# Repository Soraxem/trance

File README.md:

[This on Youtube](https://www.youtube.com/playlist?list=PL4cNBOFjqRCpjGmj9xtUntssc8VHCmmZN) | [This on Makertube](https://makertube.net/w/p/su6X6o1RSBtH18CKgF7tRq) | [This on PCBWAY](https://www.pcbway.com/project/member/shareproject/?bmbno=57956445-373F-42)

# Trance

The Trance Device Family are open hardware devices that allow life wireless lighting control via ArtNet 4. These devices mainly have applications in portable, mobile, and flexible lighting solutions.

## Control

Some lighting controllers do not implement ArtNet 4 with udp unicasting. UDP unicasting is essential for wireless lighting, because most WiFi routers ratelimit and occasionally hold back multicasted UDP packets. Unicasted UDP packets do not get ratelimited and are therefore the way to go.

If your controller does not implement UDP multicasting as per ArtNet 4 Specification, you can use my translation layer called artman. [Github Repo here](https://github.com/Soraxem/artman).

## Software

To ensure a flexible and easy software, there is a Arduino library, that implements the communication side of the software. By updating this Library with more Protocols or more reliable networking, we can expand the functionallity of every trance controller, despite hardware differences. This Library also allows for easy hardware development for DIY solutions.

You can find the Library [here on github](https://github.com/Soraxem/trance-library).

## Hardware

This project also features custom hardware that is more compact than just using a ESP32 devboard.

### USB-DMX

This device interfaces with the Eurolite Wireless DMX port on some of the newer Eurolite devices.

### PIXEL-LED

This is a led controller that can interface with the common spi-leds like ws8212. It can directly be plugged in to the usb port of a wall adapter.

## License

This Project is licensed under CERN-OHL-P

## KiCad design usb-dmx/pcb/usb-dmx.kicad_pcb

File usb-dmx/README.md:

# TRANCE USB-DMX

[Quickstart Maunual](quickstart-manual.pdf)

## Overview

The USB DMX Model is a device that has an USB plug that delivers dmx data instead of usb data. This makes the Device compatible with all DMX-over-USB devices in lighting technology.

The Company Steinigke showtechnic has some fixtures with such a Port. These Ports are originally designed for their WirelessDMX and QuickDMX devices, wich essentially are CRMX adapters. This Project is in now way affiliated with XRMC or Steinigke showtechnic.

## Usage

In The Configurations page the Artnet DMX-Address has to be set to 1, for the device to work correctly.

## Assembly

There only are smd components for this device. Here is what you need to assemble this device.

- PCBS
- Stencil
- All components from the BOM
- Tweezers
- Solder Paste
- a Plastic card
- Tissues
- SMD reflow oven or Hot Plate
- Soldering Iron
- Solder
- Masking Tape
- a Steady hand

Study the schematic and the components closely, just to be sure where and how to place each component. Then apply the Solder Paste with the Stencil, place the components and reflow the device.

## Firmware

The firmware is dependant on multible Librarys, wich are mentioned at the beginning of the file. Make sure to install the correct versions of these librarys. It also depends on the Trance library, wich is not Published in the Library Manager. To install this library, download the right version from github and put it into your arduino library Folder.

For flashing press the button on the device and plug the USB-C into the computer while keeping the button pressed. By this the microcontroller connects to the computer and expexts a software to be flashed. In arduino select the correct port and configuration, then upload the firmware.

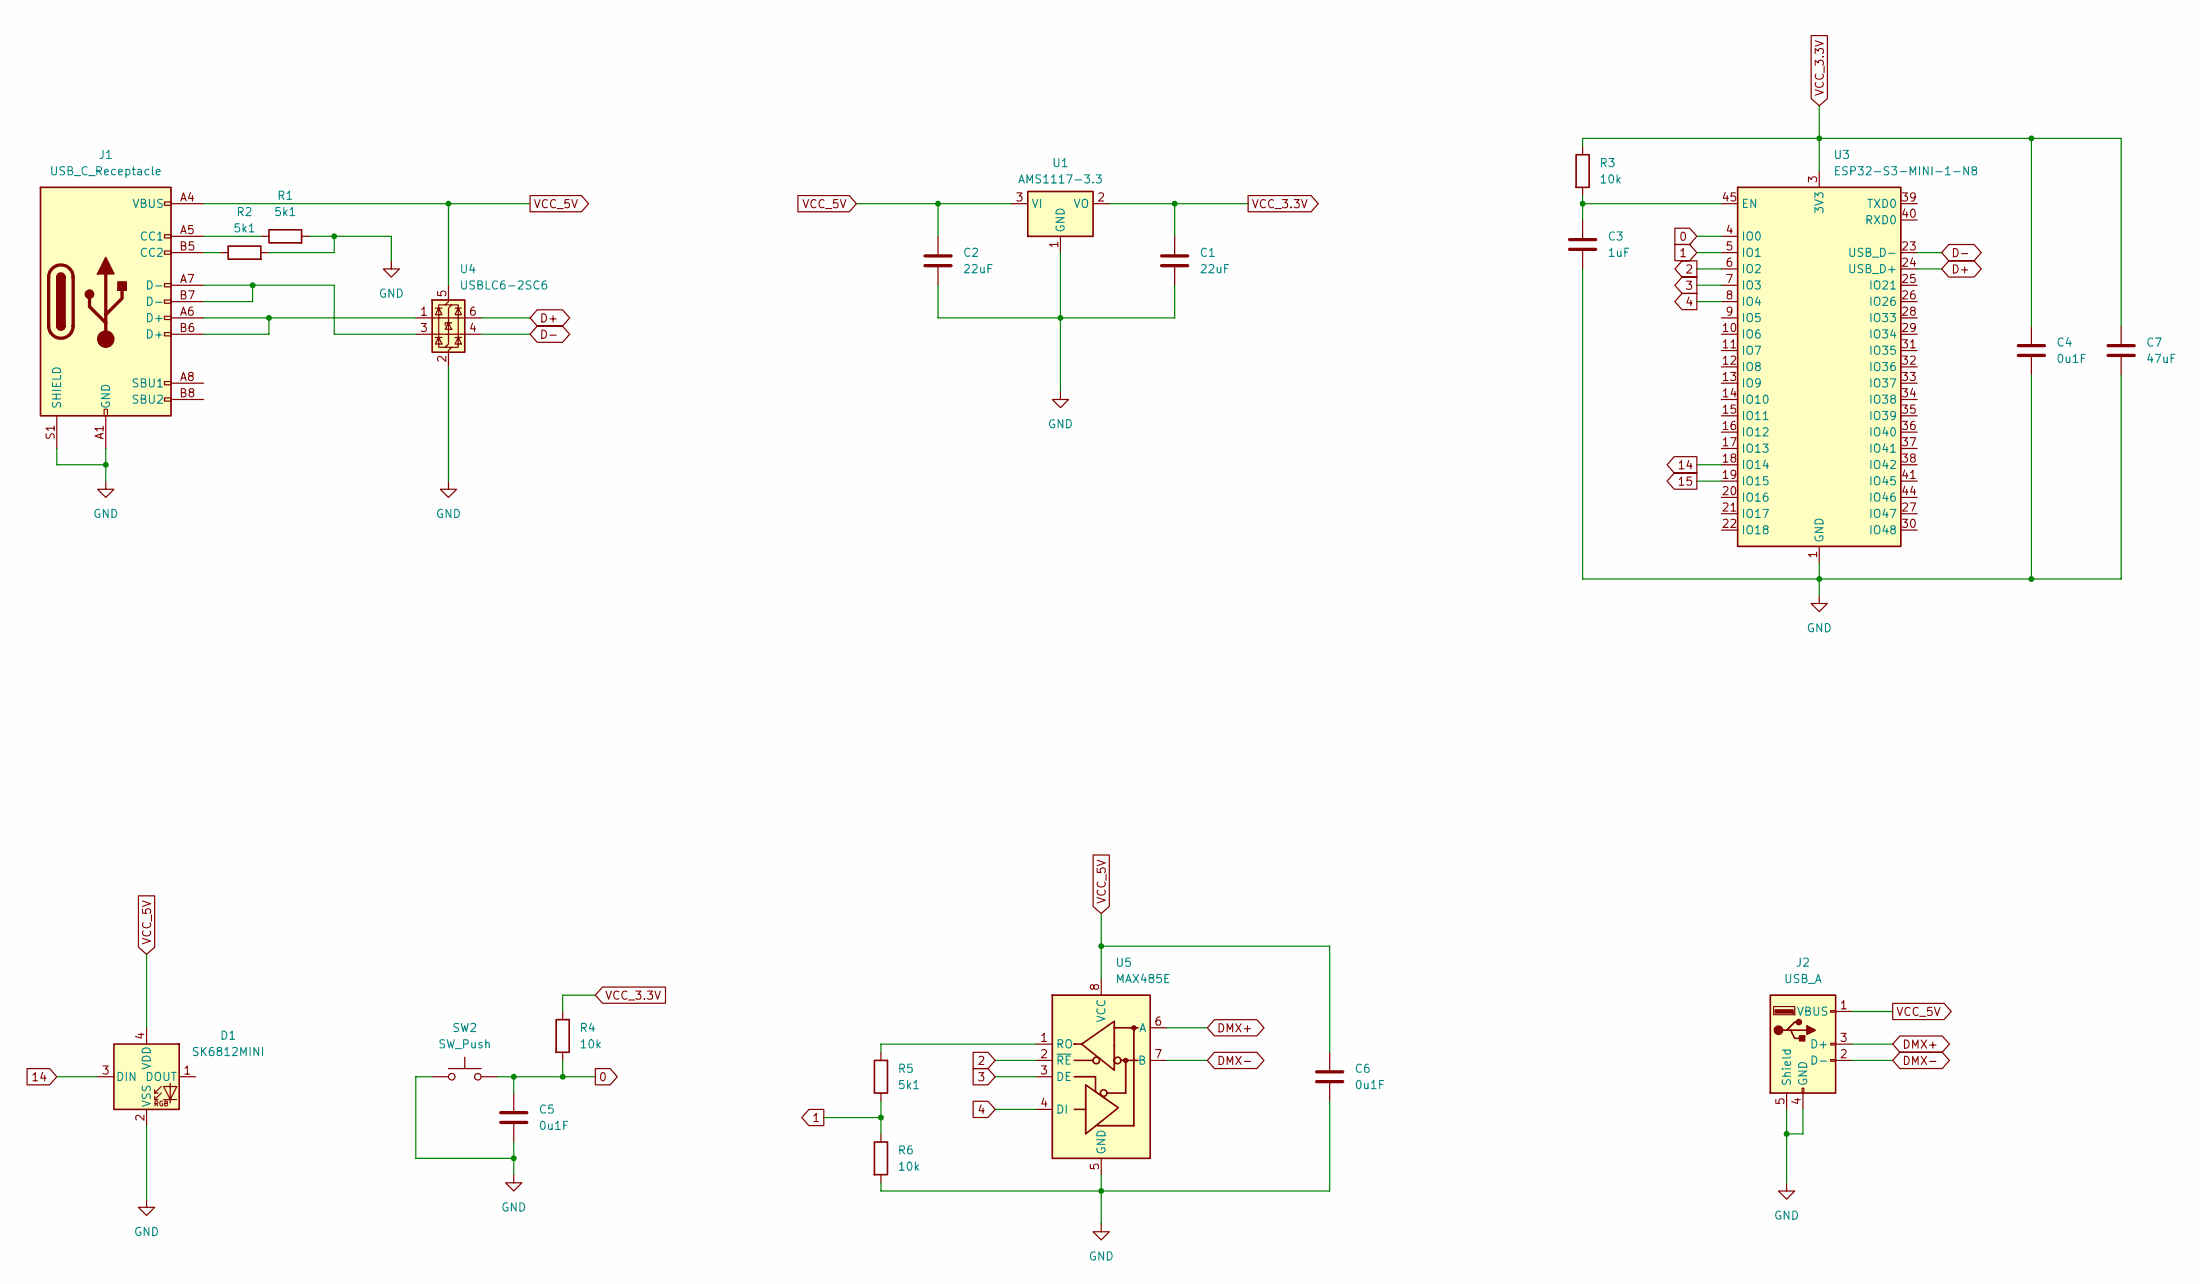
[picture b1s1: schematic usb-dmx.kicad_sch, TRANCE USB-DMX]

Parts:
C1, C2: 22uF; C_0805_2012Metric
C3: 1uF; C_0603_1608Metric_Pad1.08x0.95mm_HandSolder
C4, C6: 0u1F; C_0603_1608Metric_Pad1.08x0.95mm_HandSolder
C5: 0u1F; C_0603_1608Metric
C7: 47uF; C_0805_2012Metric_Pad1.18x1.45mm_HandSolder
D1: SK6812MINI; LED_SK6812MINI_PLCC4_3.5x3.5mm_P1.75mm
J1: USB_C_Receptacle; USB_C_Receptacle_GCT_USB4105-xx-A_16P_TopMnt_Horizontal
J2: USB_A; USB_A_CNCTech_1001-011-01101_Horizontal
R1, R2, R5: 5k1; R_0603_1608Metric_Pad0.98x0.95mm_HandSolder
R3, R6: 10k; R_0603_1608Metric_Pad0.98x0.95mm_HandSolder
R4: 10k; R_0603_1608Metric
SW2: SW_Push; SW_Push_1P1T_XKB_TS-1187A
U1: AMS1117-3.3; SOT-223-3_TabPin2
U3: ESP32-S3-MINI-1-N8; ESP32-S2-MINI-1U
U4: USBLC6-2SC6; SOT-23-6
U5: MAX485E; SOP-8_3.76x4.96mm_P1.27mm

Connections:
0: C5.1, R4.2, SW2.2, U3.4 (IO0)
1: R5.1, R6.1, U3.5 (IO1)
2: U3.6 (IO2), U5.2 (~RE)
3: U3.7 (IO3), U5.3 (DE)
4: U3.8 (IO4), U5.4 (DI)
14: D1.3 (DIN), U3.18 (IO14)
15: U3.19 (IO15)
D+: U3.24 (USB_D+), U4.6 (I/O1)
D-: U3.23 (USB_D-), U4.4 (I/O2)
DMX+: J2.3 (D+), U5.6 (A)
DMX-: J2.2 (D-), U5.7 (B)
GND: C1.2, C2.2, C3.2, C4.2, C5.2, C6.2, C7.2, D1.2 (VSS), J1.A1 (GND), J1.A12 (GND), J1.B1 (GND), J1.B12 (GND), J1.S1 (SHIELD), J2.4 (GND), J2.5 (Shield), R1.2, R2.2, R6.2, SW2.1, U1.1 (GND), U3.1 (GND), U3.2 (GND), U3.42 (GND), U3.43 (GND), U3.46 (GND), U3.47 (GND), U3.48 (GND), U3.49 (GND), U3.50 (GND), U3.51 (GND), U3.52 (GND), U3.53 (GND), U3.54 (GND), U3.55 (GND), U3.56 (GND), U3.57 (GND), U3.58 (GND), U3.59 (GND), U3.60 (GND), U3.61 (GND), U3.62 (GND), U3.63 (GND), U3.64 (GND), U3.65 (GND), U4.2 (GND), U5.5 (GND)
unnamed: J1.A5 (CC1), R1.1
unnamed: J1.B5 (CC2), R2.1
unnamed: J1.A6 (D+), J1.B6 (D+), U4.1 (I/O1)
unnamed: J1.A7 (D-), J1.B7 (D-), U4.3 (I/O2)
unnamed: C3.1, R3.2, U3.45 (EN)
unnamed: R5.2, U5.1 (RO)
VCC_3.3V: C1.1, C4.1, C7.1, R3.1, R4.1, U1.2 (VO), U3.3 (3V3)
VCC_5V: C2.1, C6.1, D1.4 (VDD), J1.A4 (VBUS), J1.A9 (VBUS), J1.B4 (VBUS), J1.B9 (VBUS), J2.1 (VBUS), U1.3 (VI), U4.5 (VBUS), U5.8 (VCC)

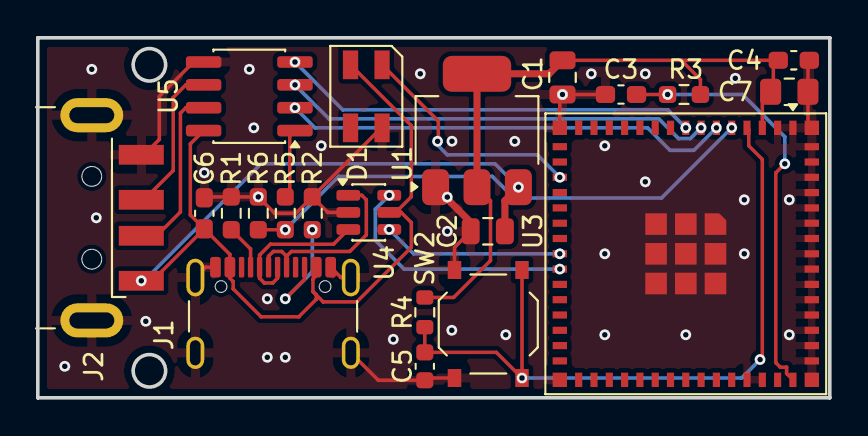
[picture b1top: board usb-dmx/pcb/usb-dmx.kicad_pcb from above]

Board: 2 copper layers, 44.0 x 20.0 mm, 21 parts (0 on the bottom side), 19 nets.

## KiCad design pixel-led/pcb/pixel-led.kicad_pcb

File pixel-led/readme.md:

# Trance PIXEL-LED

## Overview

Pixel LED is simply a Trance model that can control a spi led strip. It is designed to be directly plugged into a wall charger. It features an infrared sensor so it could be integrated with infrared remote controls.

## Sponsorship

[PCBWay](pcbway.com) was so kind to sponsor pcb production of revision 1.0 in development of this device. I quickly wanted to review their services here.

All the pcbs i recieved were up to specification and of good quality. I was suprized an honored to recieve such a sponsoring for such a small project. I admire how PCBWay invests in OpenSource electronics, especially with their project sharing platform.

## Remote

Currently there is only one Remote implemented in the Code. This remote is shipped with these [WS8212 Globe stringlights](aliexpress.com/item/1005009844838768.html), and normally interfaces with that controller.

There are firmware versions with and without the infrared Remote.

## Firmware

The firmware is dependant on multible Librarys, wich are mentioned at the beginning of the firmware source file. Make sure to install the correct versions of these librarys. It also depends on the Trance library, wich is not Published in the Library Manager. To install this library, download the right version from github and put it into your arduino library Folder.

For flashing press the button on the device and plug the USB plug into the computer while keeping the button pressed. By this the microcontroller connects to the computer and expexts a software to be flashed. In arduino select the correct port and configuration, then upload the firmware.

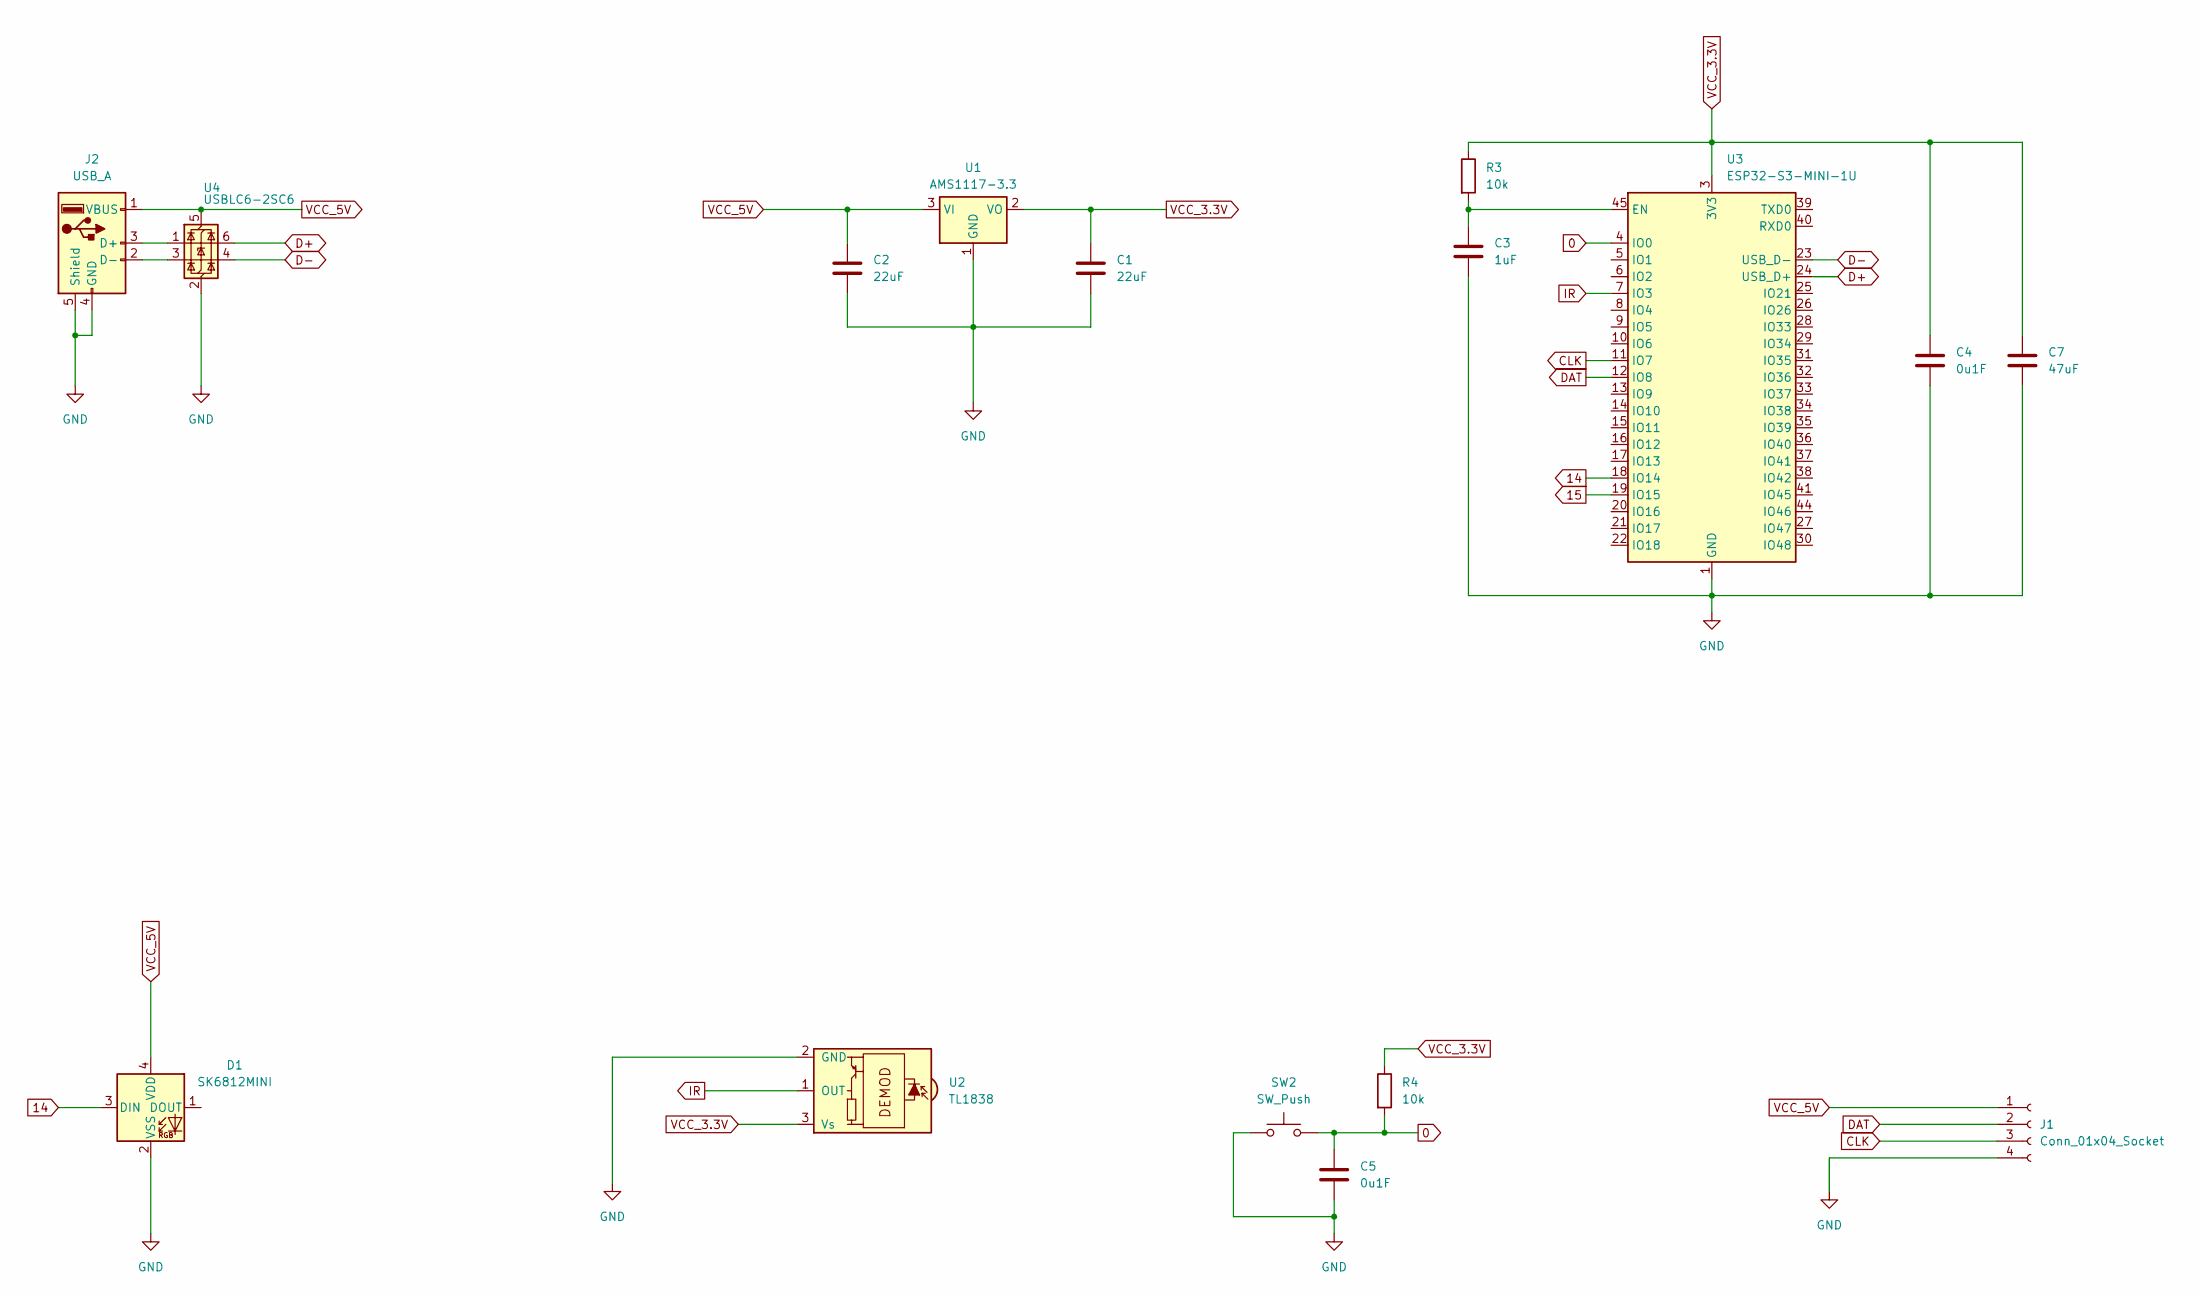
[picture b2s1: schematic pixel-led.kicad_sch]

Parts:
C1, C2: 22uF; C_0805_2012Metric
C3: 1uF; C_0603_1608Metric_Pad1.08x0.95mm_HandSolder
C4: 0u1F; C_0603_1608Metric_Pad1.08x0.95mm_HandSolder
C5: 0u1F; C_0603_1608Metric
C7: 47uF; C_0805_2012Metric_Pad1.18x1.45mm_HandSolder
D1: SK6812MINI; LED_SK6812MINI_PLCC4_3.5x3.5mm_P1.75mm
J1: Conn_01x04_Socket; PinHeader_1x04_P2.54mm_Vertical
J2: USB_A; USB_A_CNCTech_1001-011-01101_Horizontal
R3: 10k; R_0603_1608Metric_Pad0.98x0.95mm_HandSolder
R4: 10k; R_0603_1608Metric
SW2: SW_Push; SW_Push_1P1T_XKB_TS-1187A
U1: AMS1117-3.3; SOT-223-3_TabPin2
U2: TL1838; TO-92_Inline_Horizontal2
U3: ESP32-S3-MINI-1U; ESP32-S2-MINI-1
U4: USBLC6-2SC6; SOT-23-6

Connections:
0: C5.1, R4.2, SW2.2, U3.4 (IO0)
14: D1.3 (DIN), U3.18 (IO14)
15: U3.19 (IO15)
CLK: J1.3, U3.11 (IO7)
D+: U3.24 (USB_D+), U4.6 (I/O1)
D-: U3.23 (USB_D-), U4.4 (I/O2)
DAT: J1.2, U3.12 (IO8)
GND: C1.2, C2.2, C3.2, C4.2, C5.2, C7.2, D1.2 (VSS), J1.4, J2.4 (GND), J2.5 (Shield), SW2.1, U1.1 (GND), U2.2 (GND), U3.1 (GND), U3.2 (GND), U3.42 (GND), U3.43 (GND), U3.46 (GND), U3.47 (GND), U3.48 (GND), U3.49 (GND), U3.50 (GND), U3.51 (GND), U3.52 (GND), U3.53 (GND), U3.54 (GND), U3.55 (GND), U3.56 (GND), U3.57 (GND), U3.58 (GND), U3.59 (GND), U3.60 (GND), U3.61 (GND), U3.62 (GND), U3.63 (GND), U3.64 (GND), U3.65 (GND), U4.2 (GND)
IR: U2.1 (OUT), U3.7 (IO3)
unnamed: J2.3 (D+), U4.1 (I/O1)
unnamed: J2.2 (D-), U4.3 (I/O2)
unnamed: C3.1, R3.2, U3.45 (EN)
VCC_3.3V: C1.1, C4.1, C7.1, R3.1, R4.1, U1.2 (VO), U2.3 (Vs), U3.3 (3V3)
VCC_5V: C2.1, D1.4 (VDD), J1.1, J2.1 (VBUS), U1.3 (VI), U4.5 (VBUS)

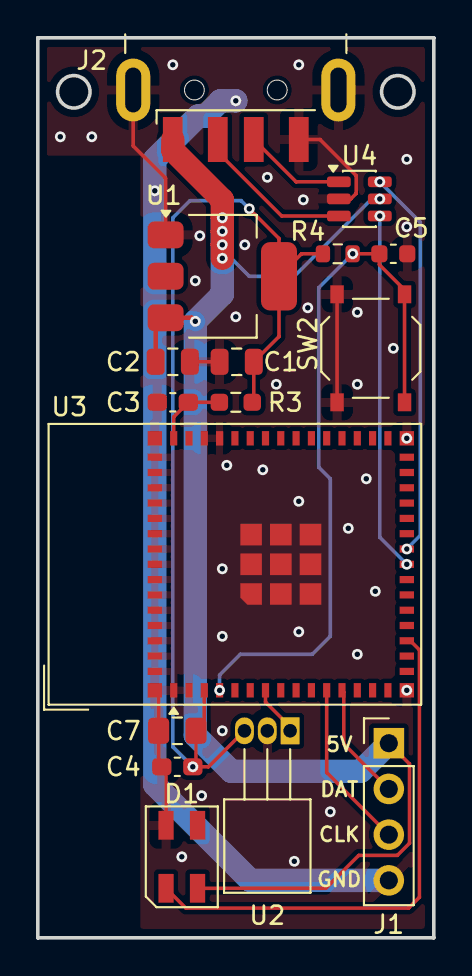
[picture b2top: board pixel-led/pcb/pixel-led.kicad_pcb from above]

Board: 2 copper layers, 22.0 x 50.0 mm, 16 parts (0 on the bottom side), 13 nets.

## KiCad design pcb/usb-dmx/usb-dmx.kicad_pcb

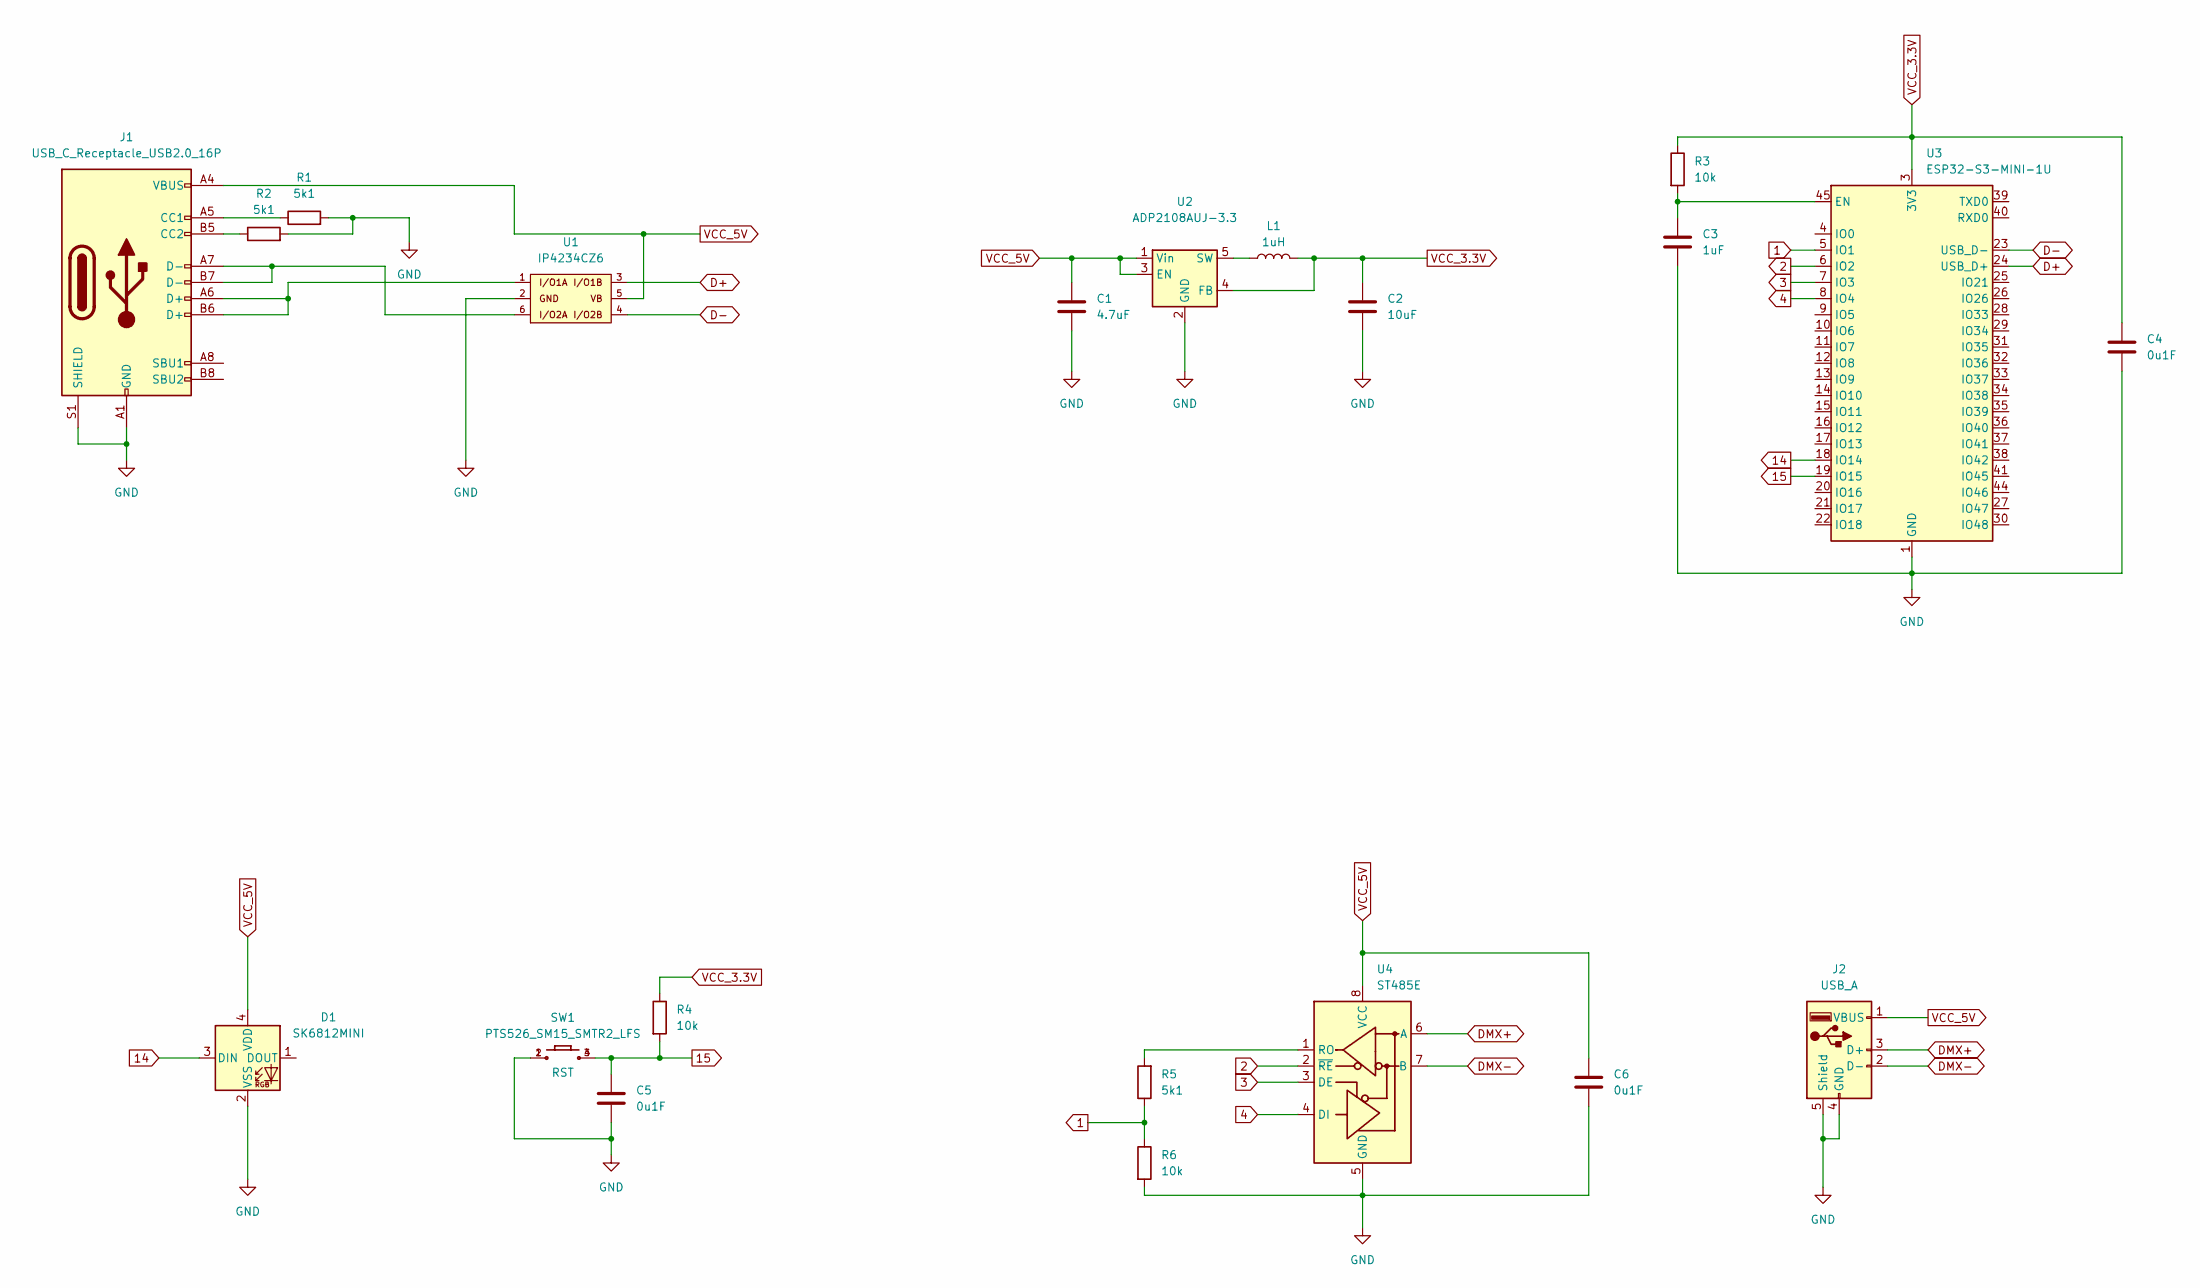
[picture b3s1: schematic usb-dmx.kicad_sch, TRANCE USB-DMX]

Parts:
C1: 4.7uF; C_0603_1608Metric; MOUSER_PART_NUMBER 187-CL10A475KO8NNNC
C2: 10uF; C_0805_2012Metric; MOUSER_PART_NUMBER 187-CL21A106KOQNNNF
C3: 1uF; C_0603_1608Metric_Pad1.08x0.95mm_HandSolder; MOUSER_PART_NUMBER 187-CL05F104ZO5NNND
C4, C5, C6: 0u1F; C_0603_1608Metric_Pad1.08x0.95mm_HandSolder; MOUSER_PART_NUMBER 187-CL05F104ZO5NNND
D1: SK6812MINI; LED_SK6812MINI_PLCC4_3.5x3.5mm_P1.75mm
J1: USB_C_Receptacle_USB2.0_16P; USB_C_Receptacle_GCT_USB4110
J2: USB_A; USB_A_Molex_48037-2200_Horizontal
L1: 1uH; L_0805_2012Metric; MOUSER_PART_NUMBER 81-LQM21PN1R0MC0D
R1, R2, R5: 5k1; R_0603_1608Metric_Pad0.98x0.95mm_HandSolder; MOUSER_PART_NUMBER 71-CRCW0402-5.1K-E3
R3, R4, R6: 10k; R_0603_1608Metric_Pad0.98x0.95mm_HandSolder; MOUSER_PART_NUMBER 71-CRCW0402-10K-E3
SW1: PTS526_SM15_SMTR2_LFS; PTS526SM15SMTR2LFS; MOUSER_PART_NUMBER 611-PTS526SM15SMTR2L
U1: IP4234CZ6; IP4234CZ6_SOT-457-6; MOUSER_PART_NUMBER 771-IP4234CZ6
U2: ADP2108AUJ-3.3; TSOT-23-5; MOUSER_PART_NUMBER 584-ADP2108AUJZ3.3R7
U3: ESP32-S3-MINI-1U; ESP32-S2-MINI-1U; MOUSER_PART_NUMBER 356-ESP32S3MINI1UN8
U4: ST485E; SOIC-8_3.9x4.9mm_P1.27mm

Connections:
1: R5.1, R6.1, U3.5 (IO1)
2: U3.6 (IO2), U4.2 (~RE)
3: U3.7 (IO3), U4.3 (DE)
4: U3.8 (IO4), U4.4 (DI)
14: D1.3 (DIN), U3.18 (IO14)
15: C5.1, R4.2, SW1.3, SW1.4, U3.19 (IO15)
D+: U1.3, U3.24 (USB_D+)
D-: U1.4, U3.23 (USB_D-)
DMX+: J2.3 (D+), U4.6 (A)
DMX-: J2.2 (D-), U4.7 (B)
GND: C1.2, C2.2, C3.2, C4.2, C5.2, C6.2, D1.2 (VSS), J1.A1 (GND), J1.A12 (GND), J1.B1 (GND), J1.B12 (GND), J1.S1 (SHIELD), J2.4 (GND), J2.5 (Shield), R1.2, R2.2, R6.2, SW1.1, SW1.2, U1.2, U2.2 (GND), U3.1 (GND), U3.2 (GND), U3.42 (GND), U3.43 (GND), U3.46 (GND), U3.47 (GND), U3.48 (GND), U3.49 (GND), U3.50 (GND), U3.51 (GND), U3.52 (GND), U3.53 (GND), U3.54 (GND), U3.55 (GND), U3.56 (GND), U3.57 (GND), U3.58 (GND), U3.59 (GND), U3.60 (GND), U3.61 (GND), U3.62 (GND), U3.63 (GND), U3.64 (GND), U3.65 (GND), U4.5 (GND)
unnamed: J1.A5 (CC1), R1.1
unnamed: J1.B5 (CC2), R2.1
unnamed: J1.A6 (D+), J1.B6 (D+), U1.1
unnamed: J1.A7 (D-), J1.B7 (D-), U1.6
unnamed: L1.1, U2.5 (SW)
unnamed: C3.1, R3.2, U3.45 (EN)
unnamed: R5.2, U4.1 (RO)
VCC_3.3V: C2.1, C4.1, L1.2, R3.1, R4.1, U2.4 (FB), U3.3 (3V3)
VCC_5V: C1.1, C6.1, D1.4 (VDD), J1.A4 (VBUS), J1.A9 (VBUS), J1.B4 (VBUS), J1.B9 (VBUS), J2.1 (VBUS), U1.5, U2.1 (Vin), U2.3 (EN), U4.8 (VCC)

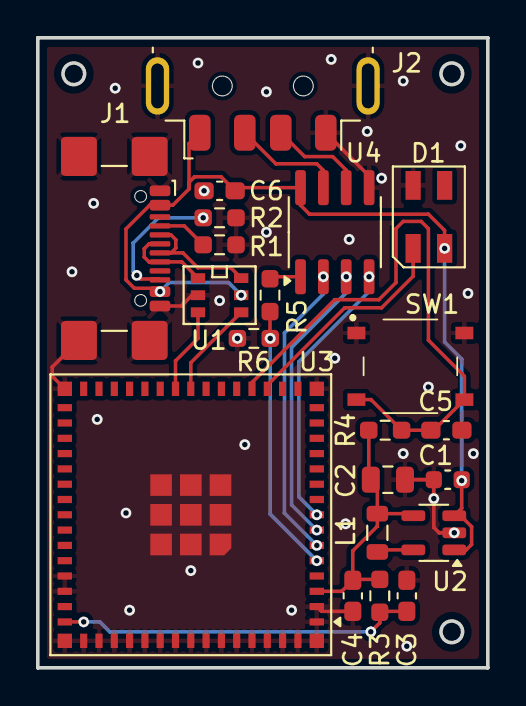
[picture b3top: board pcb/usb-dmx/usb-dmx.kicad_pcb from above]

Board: 2 copper layers, 25.0 x 35.0 mm, 21 parts (0 on the bottom side), 20 nets.

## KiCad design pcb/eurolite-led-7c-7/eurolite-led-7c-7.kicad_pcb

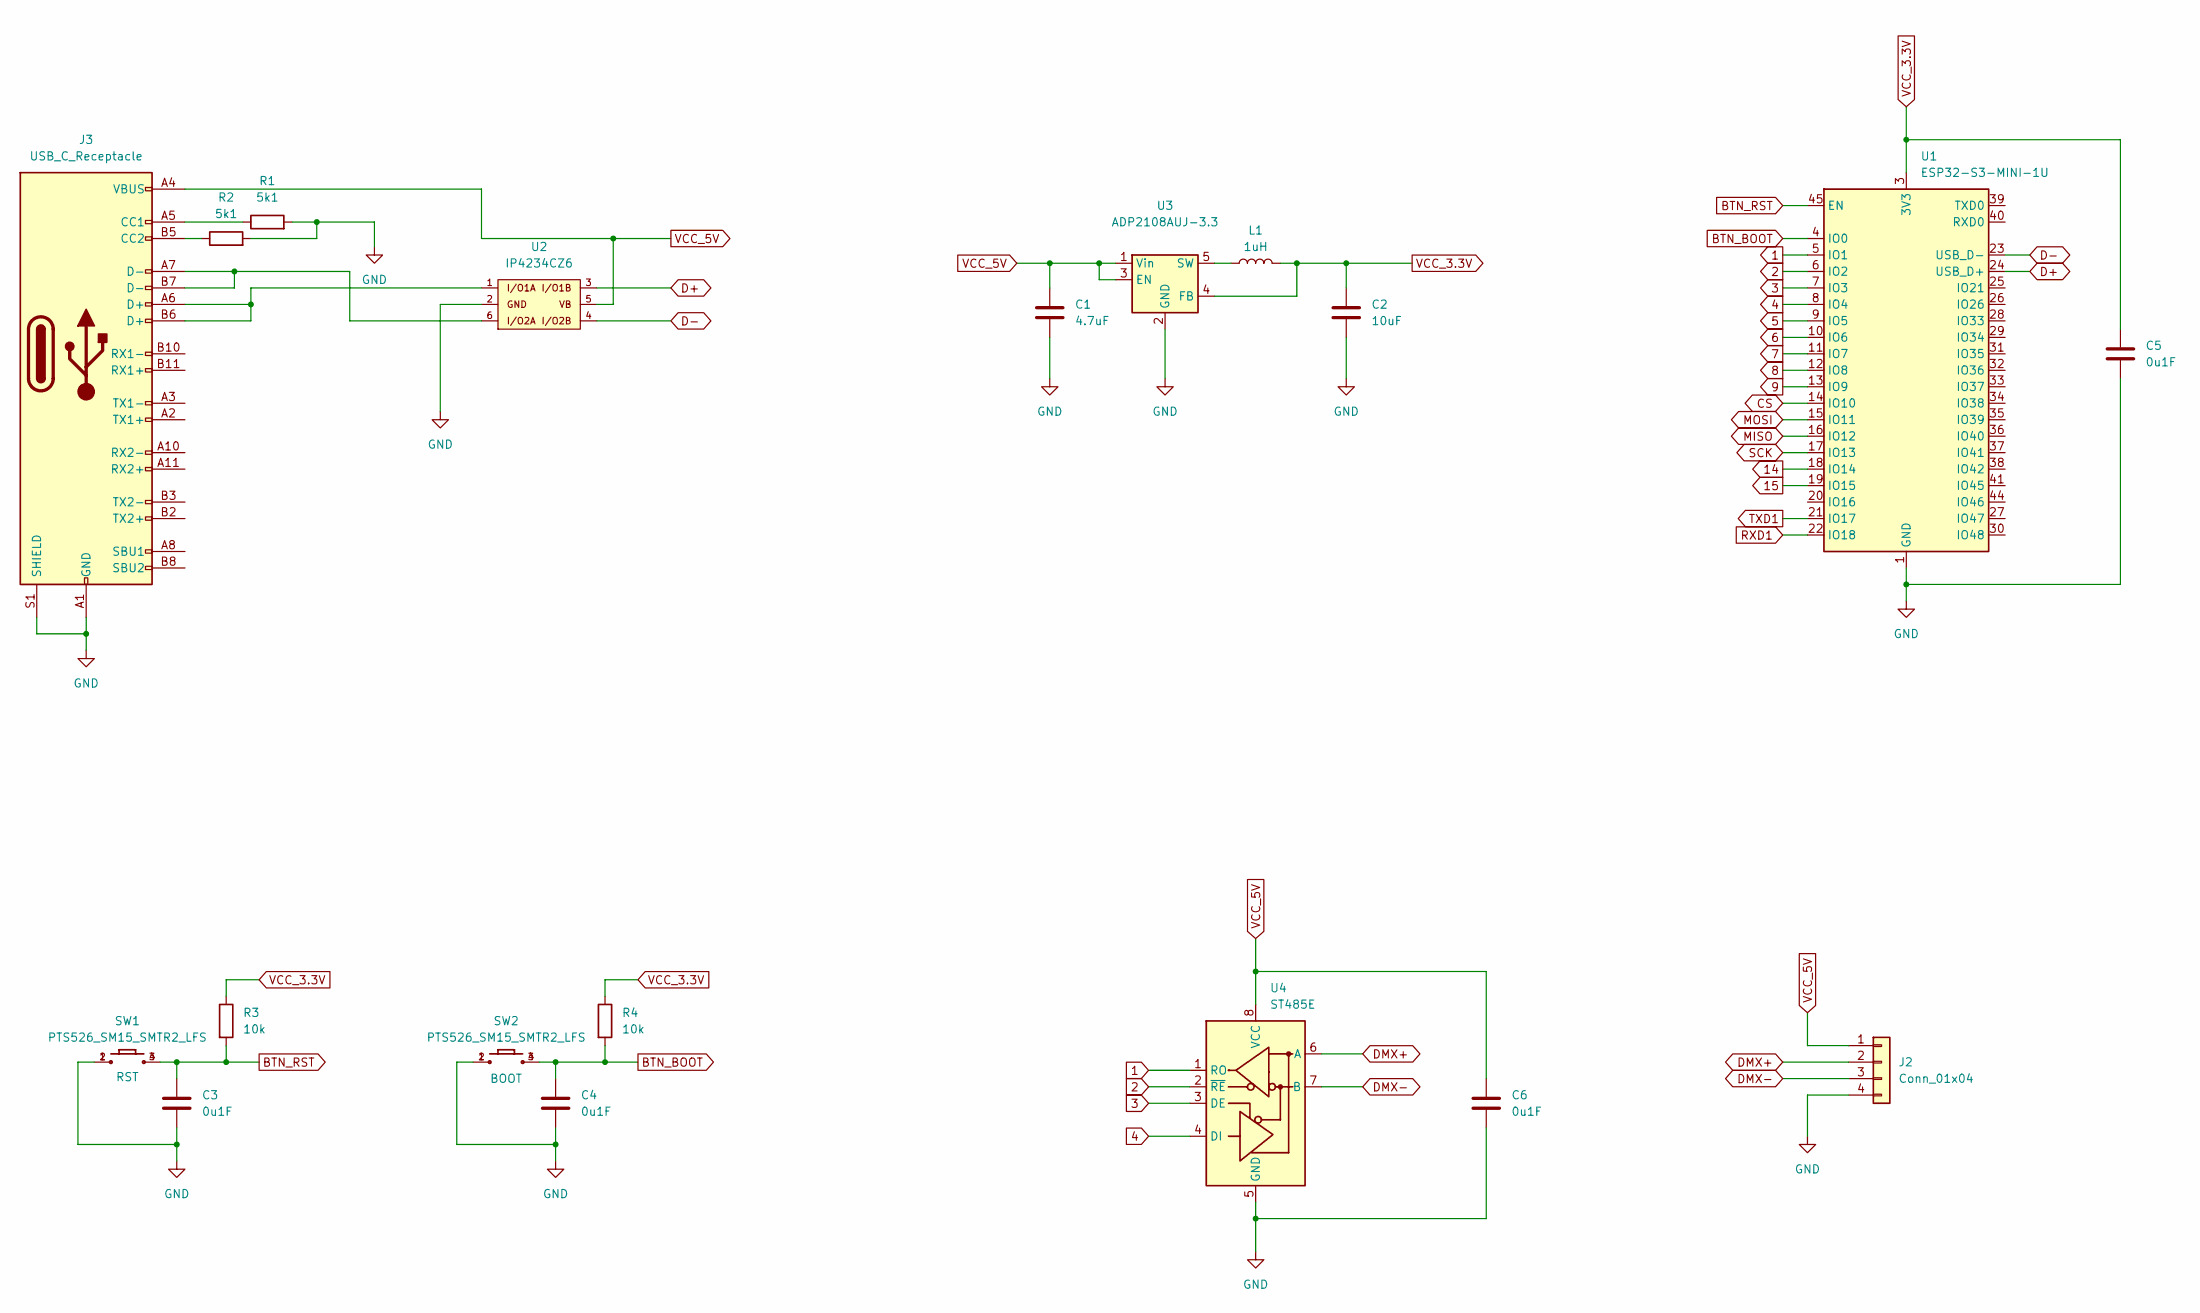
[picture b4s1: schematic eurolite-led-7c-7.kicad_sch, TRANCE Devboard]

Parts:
C1: 4.7uF; C_0603_1608Metric; MOUSER_PART_NUMBER 187-CL10A475KO8NNNC
C2: 10uF; C_0805_2012Metric; MOUSER_PART_NUMBER 187-CL21A106KOQNNNF
C3, C4, C5, C6: 0u1F; C_0603_1608Metric_Pad1.08x0.95mm_HandSolder; MOUSER_PART_NUMBER 187-CL05F104ZO5NNND
J2: Conn_01x04; JST_PH_B4B-PH-K_1x04_P2.00mm_Vertical
J3: USB_C_Receptacle; USB_C_Receptacle_GCT_USB4115-03-C
L1: 1uH; L_0805_2012Metric; MOUSER_PART_NUMBER 81-LQM21PN1R0MC0D
R1, R2: 5k1; R_0603_1608Metric_Pad0.98x0.95mm_HandSolder; MOUSER_PART_NUMBER 71-CRCW0402-5.1K-E3
R3, R4: 10k; R_0603_1608Metric_Pad0.98x0.95mm_HandSolder; MOUSER_PART_NUMBER 71-CRCW0402-10K-E3
SW1, SW2: PTS526_SM15_SMTR2_LFS; PTS526SM15SMTR2LFS; MOUSER_PART_NUMBER 611-PTS526SM15SMTR2L
U1: ESP32-S3-MINI-1U; ESP32-S2-MINI-1U; MOUSER_PART_NUMBER 356-ESP32S3MINI1UN8
U2: IP4234CZ6; IP4234CZ6_SOT-457-6; MOUSER_PART_NUMBER 771-IP4234CZ6
U3: ADP2108AUJ-3.3; TSOT-23-5; MOUSER_PART_NUMBER 584-ADP2108AUJZ3.3R7
U4: ST485E; SOIC-8_3.9x4.9mm_P1.27mm

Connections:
1: U1.5 (IO1), U4.1 (RO)
2: U1.6 (IO2), U4.2 (~RE)
3: U1.7 (IO3), U4.3 (DE)
4: U1.8 (IO4), U4.4 (DI)
5: U1.9 (IO5)
6: U1.10 (IO6)
7: U1.11 (IO7)
8: U1.12 (IO8)
9: U1.13 (IO9)
14: U1.18 (IO14)
15: U1.19 (IO15)
BTN_BOOT: C4.1, R4.2, SW2.3, SW2.4, U1.4 (IO0)
BTN_RST: C3.1, R3.2, SW1.3, SW1.4, U1.45 (EN)
CS: U1.14 (IO10)
D+: U1.24 (USB_D+), U2.3
D-: U1.23 (USB_D-), U2.4
DMX+: J2.2, U4.6 (A)
DMX-: J2.3, U4.7 (B)
GND: C1.2, C2.2, C3.2, C4.2, C5.2, C6.2, J2.4, J3.A1 (GND), J3.A12 (GND), J3.B1 (GND), J3.B12 (GND), J3.S1 (SHIELD), R1.2, R2.2, SW1.1, SW1.2, SW2.1, SW2.2, U1.1 (GND), U1.2 (GND), U1.42 (GND), U1.43 (GND), U1.46 (GND), U1.47 (GND), U1.48 (GND), U1.49 (GND), U1.50 (GND), U1.51 (GND), U1.52 (GND), U1.53 (GND), U1.54 (GND), U1.55 (GND), U1.56 (GND), U1.57 (GND), U1.58 (GND), U1.59 (GND), U1.60 (GND), U1.61 (GND), U1.62 (GND), U1.63 (GND), U1.64 (GND), U1.65 (GND), U2.2, U3.2 (GND), U4.5 (GND)
MISO: U1.16 (IO12)
MOSI: U1.15 (IO11)
unnamed: J3.A5 (CC1), R1.1
unnamed: J3.B5 (CC2), R2.1
unnamed: J3.A6 (D+), J3.B6 (D+), U2.1
unnamed: J3.A7 (D-), J3.B7 (D-), U2.6
unnamed: L1.1, U3.5 (SW)
RXD1: U1.22 (IO18)
SCK: U1.17 (IO13)
TXD1: U1.21 (IO17)
VCC_3.3V: C2.1, C5.1, L1.2, R3.1, R4.1, U1.3 (3V3), U3.4 (FB)
VCC_5V: C1.1, C6.1, J2.1, J3.A4 (VBUS), J3.A9 (VBUS), J3.B4 (VBUS), J3.B9 (VBUS), U2.5, U3.1 (Vin), U3.3 (EN), U4.8 (VCC)

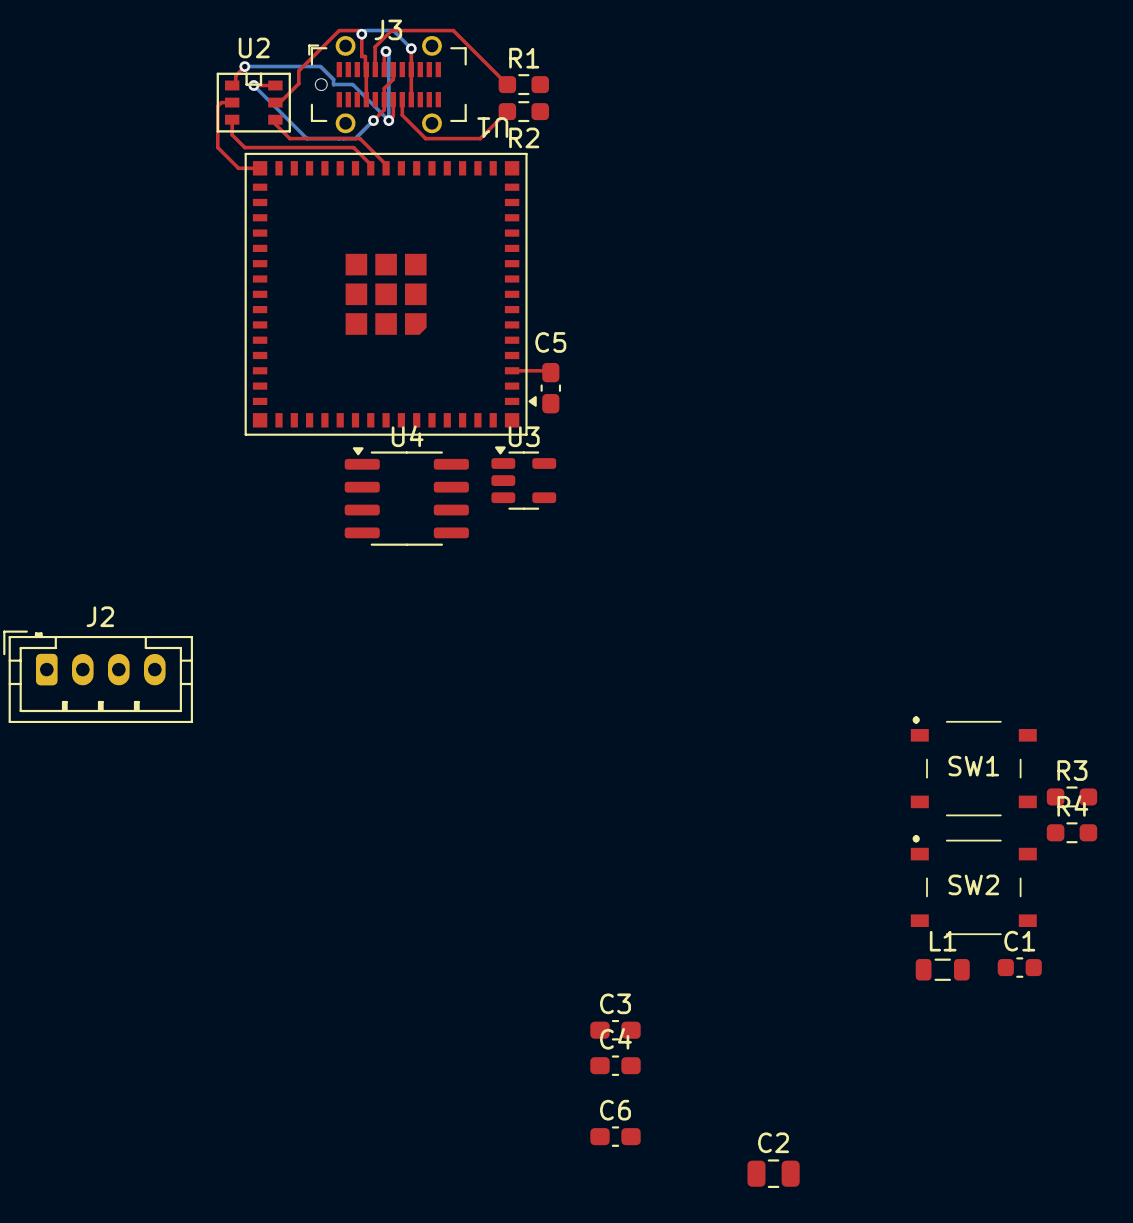
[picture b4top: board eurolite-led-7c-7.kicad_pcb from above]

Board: 2 copper layers, 19 parts (0 on the bottom side), 18 nets.

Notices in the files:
usb-dmx/pcb/usb-dmx.kicad_pcb:
License: CERN OHL-P
